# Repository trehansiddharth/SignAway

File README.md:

# SignAway

SignAway is a completely handheld probe that you can swipe over two signatures to algorithmically verify that they came from the same person. It is my final project for MIT's 6.115 course (Microcontrollers Lab).

## Directory Structure

- `./Background`: Background information on the algorithms used, such as SLAM and neural networks for signature verification.
- `./Datasheets`: Datasheets for the electronic components.
- `./Designs`: Schematics, board layouts, and CAD sketches for hardware.
- `./Logs`: Pictures, log files, and notes taken during development of SignAway to keep track of things.
- `./Source`: Source code running on the 2051 and PSoC.

## Disclaimer

Right now this is a work in progress. The deadline for completion is the end of May.

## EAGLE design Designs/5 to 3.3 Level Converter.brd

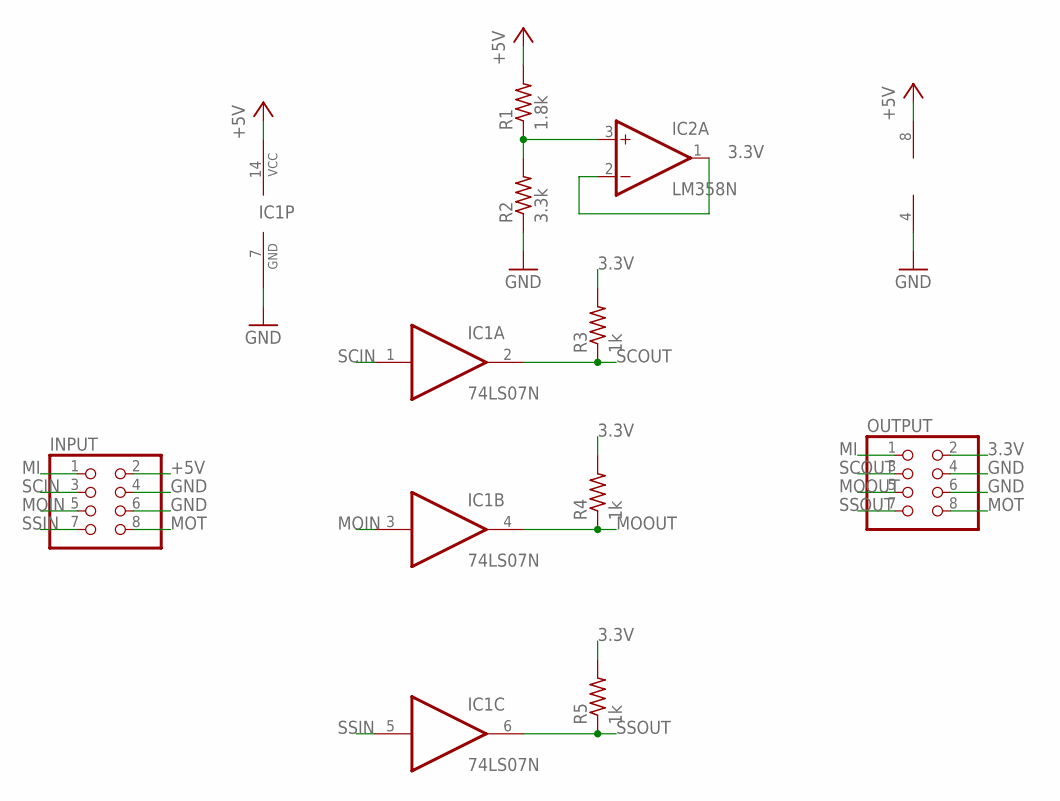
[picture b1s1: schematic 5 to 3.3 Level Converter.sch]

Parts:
IC1: 74LS07N; DIL14
IC2: LM358N; DIL08
INPUT: PINHD-2X4; 2X04
OUTPUT: PINHD-2X4; 2X04
R1: 1.8k; 0207/7
R2: 3.3k; 0207/7
R3, R4, R5: 1k; 0207/7

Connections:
3.3V: IC2.1 (OUT), IC2.2 (-IN), OUTPUT.2, R3.2, R4.2, R5.2
+5V: IC1.14 (VCC), IC2.8 (V+), INPUT.2, R1.2
GND: IC1.7 (GND), IC2.4 (V-), INPUT.4, INPUT.6, OUTPUT.4, OUTPUT.6, R2.1
MI: INPUT.1, OUTPUT.1
MOIN: IC1.3 (I), INPUT.5
MOOUT: IC1.4 (O), OUTPUT.5, R4.1
MOT: INPUT.8, OUTPUT.8
unnamed: IC2.3 (+IN), R1.1, R2.2
SCIN: IC1.1 (I), INPUT.3
SCOUT: IC1.2 (O), OUTPUT.3, R3.1
SSIN: IC1.5 (I), INPUT.7
SSOUT: IC1.6 (O), OUTPUT.7, R5.1

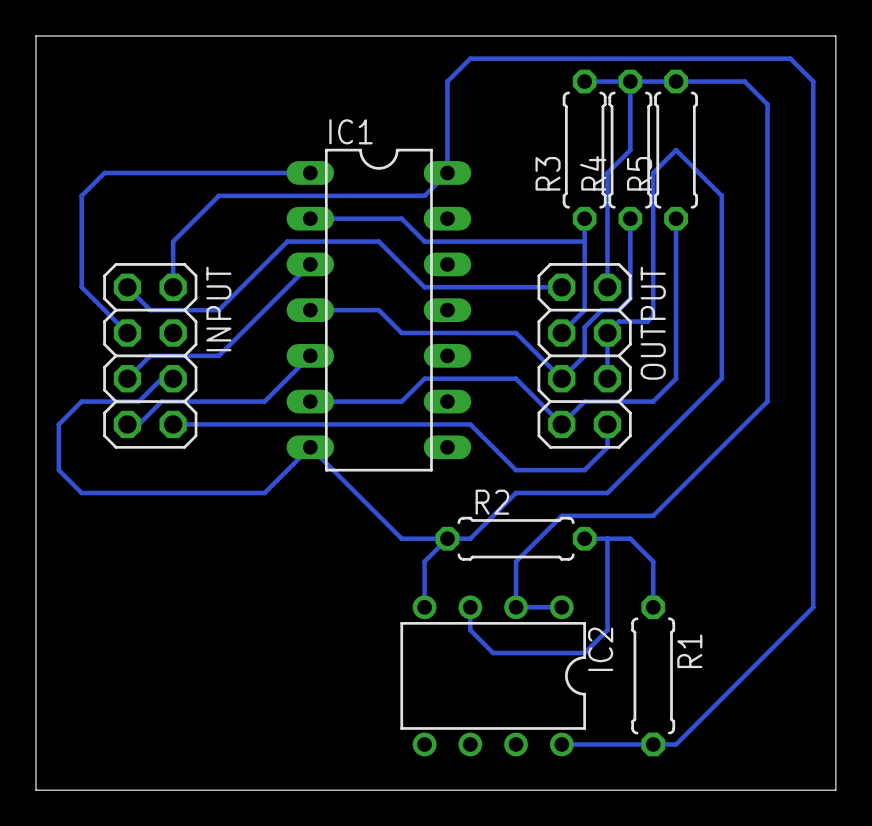
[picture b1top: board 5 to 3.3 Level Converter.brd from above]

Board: 2 copper layers, 44.4 x 41.9 mm, 9 parts (0 on the bottom side), 12 nets.

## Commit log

2016-04-18 Made first (untested) prototype of ADNS-9800 REPL
2016-04-20 Rearranged files, added datasheets, made a schematic, started PSoC project
2016-04-20 No major changes, just tested PyInstaller
2016-04-20 Tested on 8051, got write_adns to work, read_adns still does not properly read
2016-04-21 Modified source to be able to target different MCS-51 microcontrollers
2016-04-21 Got adns_read to work!
2016-04-24 First mechanical prototypes
2016-04-25 Minor changes to mechanicals
2016-04-27 Started work on image burst mode
2016-04-27 Added boards and schematics for ADNS-9800 breakout board
2016-04-27 Wrote image burst over serial code for testing
2016-04-28 Made progress on image burst
2016-04-28 Got image burst to work!
2016-04-28 Wrote testing motion burst code, refactored testing image burst code, wrote image visualizer
2016-04-29 Small changes to motion and image burst, started motion.asm
2016-05-03 Did testing work for motion.asm
2016-05-03 Made some progress in simple motion reporting
2016-05-04 Wrote a test version of motion.asm based on motion burst
2016-05-04 Made level converter Eagle file, minor changes to motion.asm and psoc.lib.asm
2016-05-05 Started work on PSoC component
2016-05-06 Wrote testing code for motion.asm that checks changes in absolute position and sends them to the PSoC
2016-05-06 Got motion.asm to fire after a certain manhattan distance is traversed
2016-05-07 Fixed stack issue courtesy of Alex Huang
2016-05-08 Did some work on design, PSoC, motion.asm, and desktop MATLAB interface
2016-05-09 Got SPI communication with PSoC working
2016-05-09 Got PSoC to send data to MATLAB
2016-05-09 Added SPI interrupts to PSoC code
2016-05-10 Got interrupts on PSoC working with switches and buttons
2016-05-11 Minor modifications to motion.asm
2016-05-11 Made PSoC talk to MATLAB to visualize signature
2016-05-12 Got signature verify to work and signature forge to implement a simple algorithm but not really work
2016-05-12 Modified viewImage.m slightly, added image captures to logs
2016-05-13 Wrote lab report -- done! :)
